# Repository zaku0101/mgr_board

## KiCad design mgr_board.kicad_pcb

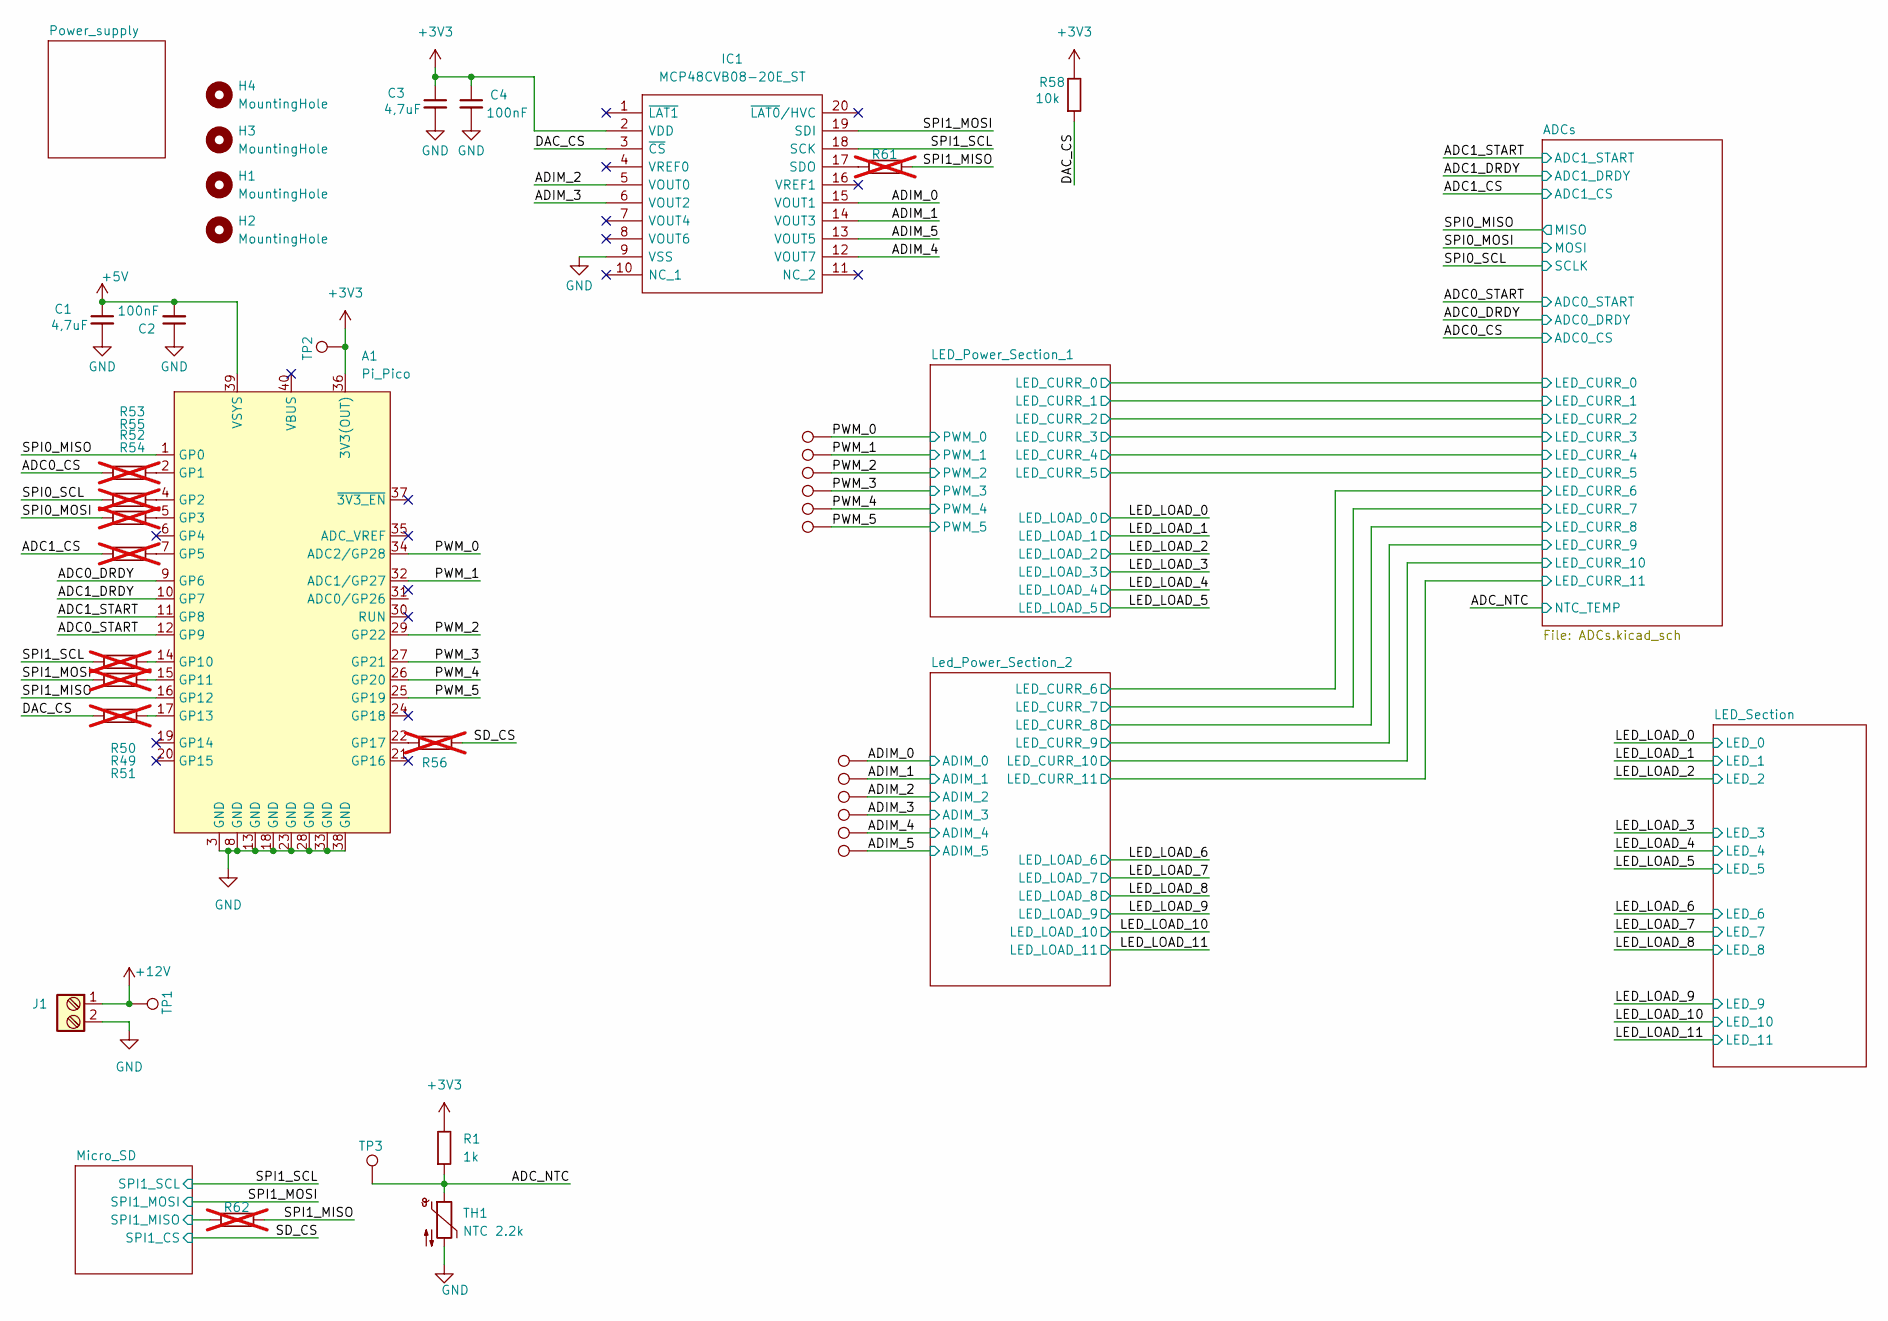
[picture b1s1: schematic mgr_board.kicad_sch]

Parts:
A1: Pi_Pico; RaspberryPi_Pico_Common_THT
C1, C3: 4,7uF; C_0603_1608Metric_Pad1.08x0.95mm_HandSolder; LCSC C19666
C2, C4: 100nF; C_0603_1608Metric_Pad1.08x0.95mm_HandSolder; LCSC C14663
H1, H2, H3, H4: MountingHole; MountingHole_3.2mm_M3
IC1: MCP48CVB08-20E_ST; TSSOP-20_4.4x6.5mm_P0.65mm; Manufacturer_Part_Number MCP48CVB08-20E/ST
J1: Screw_Terminal_2_P5.00mm; TerminalBlock_bornier-2_P5.08mm
R1: 1k; R_0603_1608Metric_Pad0.98x0.95mm_HandSolder; LCSC C21190
R49, R50, R51, R52, R53, R54, R55, R56, R61, R62: NMT; R_0402_1005Metric; not fitted
R58: 10k; R_0603_1608Metric_Pad0.98x0.95mm_HandSolder; LCSC C25804
TH1: NTC 2.2k; R_0805_2012Metric_Pad1.20x1.40mm_HandSolder
TP1, TP2, TP3, TP4, TP5, TP6, TP7, TP8, TP9, TP10, TP11, TP12, TP13, TP14, TP15: TestPoint; TestPoint_Pad_D2.0mm

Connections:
+3V3: A1.36 (3V3(OUT)), C3.1, C4.1, IC1.2 (VDD), R1.2, R58.2, TP2.1; also elsewhere on the board
+5V: A1.39 (VSYS), C1.1, C2.2; also elsewhere on the board
+12V: J1.1, TP1.1; also elsewhere on the board
/ADC0_CS: R55.2; also elsewhere on the board
/ADC0_DRDY: A1.9 (GP6); also elsewhere on the board
/ADC0_START: A1.12 (GP9); also elsewhere on the board
/ADC1_CS: R54.2; also elsewhere on the board
/ADC1_DRDY: A1.10 (GP7); also elsewhere on the board
/ADC1_START: A1.11 (GP8); also elsewhere on the board
/ADC_NTC: R1.1, TH1.1, TP3.1; also elsewhere on the board
/ADIM_0: IC1.15 (VOUT1), TP10.1; also elsewhere on the board
/ADIM_1: IC1.14 (VOUT3), TP11.1; also elsewhere on the board
/ADIM_2: IC1.5 (VOUT0), TP12.1; also elsewhere on the board
/ADIM_3: IC1.6 (VOUT2), TP13.1; also elsewhere on the board
/ADIM_4: IC1.12 (VOUT7), TP14.1; also elsewhere on the board
/ADIM_5: IC1.13 (VOUT5), TP15.1; also elsewhere on the board
/DAC_CS: IC1.3 (~CS), R51.2, R58.1
/Micro_SD/SPI1_MISO: R62.2; also elsewhere on the board
/PWM_0: A1.34 (ADC2/GP28), TP4.1; also elsewhere on the board
/PWM_1: A1.32 (ADC1/GP27), TP5.1; also elsewhere on the board
/PWM_2: A1.29 (GP22), TP6.1; also elsewhere on the board
/PWM_3: A1.27 (GP21), TP7.1; also elsewhere on the board
/PWM_4: A1.26 (GP20), TP8.1; also elsewhere on the board
/PWM_5: A1.25 (GP19), TP9.1; also elsewhere on the board
/SD_CS: R56.1; also elsewhere on the board
/SPI0_MISO: A1.1 (GP0); also elsewhere on the board
/SPI0_MOSI: R52.2; also elsewhere on the board
/SPI0_SCL: R53.2; also elsewhere on the board
/SPI1_MISO: A1.16 (GP12), R61.1, R62.1
/SPI1_MOSI: IC1.19 (SDI), R49.2; also elsewhere on the board
/SPI1_SCL: IC1.18 (SCK), R50.2; also elsewhere on the board
GND: A1.3 (GND), A1.8 (GND), A1.13 (GND), A1.18 (GND), A1.23 (GND), A1.28 (GND), A1.33 (GND), A1.38 (GND), C1.2, C2.1, C3.2, C4.2, IC1.9 (VSS), J1.2, TH1.2; also elsewhere on the board
unnamed: A1.2 (GP1), R55.1
unnamed: A1.4 (GP2), R53.1
unnamed: A1.5 (GP3), R52.1
unnamed: A1.7 (GP5), R54.1
unnamed: A1.14 (GP10), R50.1
unnamed: A1.15 (GP11), R49.1
unnamed: A1.17 (GP13), R51.1
unnamed: A1.22 (GP17), R56.2
unnamed: IC1.17 (SDO), R61.2

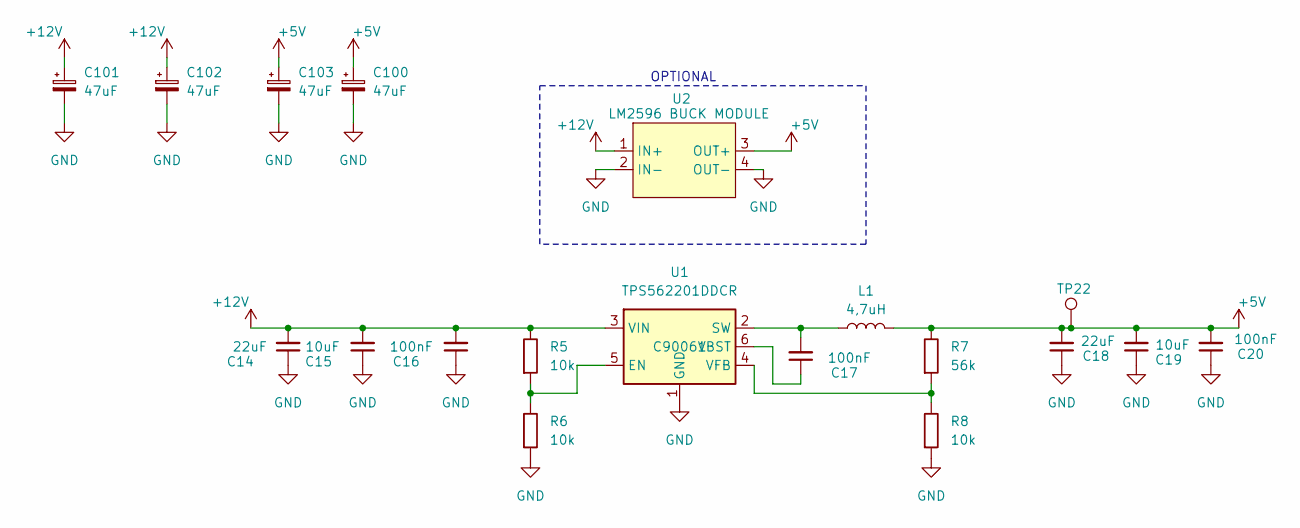
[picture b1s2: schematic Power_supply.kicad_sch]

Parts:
C14, C18: 22uF; C_0805_2012Metric_Pad1.18x1.45mm_HandSolder; LCSC C96446
C15, C19: 10uF; C_0603_1608Metric_Pad1.08x0.95mm_HandSolder; LCSC C45783
C16, C17, C20: 100nF; C_0603_1608Metric_Pad1.08x0.95mm_HandSolder; LCSC C14663
C100, C101, C102, C103: 47uF; CP_EIA-6032-15_Kemet-U_Pad2.25x2.35mm_HandSolder
L1: 4,7uH; HPIO530-4R7; LCSC C408410
R5, R6, R8: 10k; R_0603_1608Metric_Pad0.98x0.95mm_HandSolder; LCSC C25804
R7: 56k; R_0603_1608Metric_Pad0.98x0.95mm_HandSolder; LCSC C23206
TP22: TestPoint; TestPoint_Pad_D2.0mm
U1: TPS562201DDCR; SOT-23-6_Handsoldering; LCSC C90061
U2: LM2596 BUCK MODULE; LM2596 DC-DC module

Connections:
+5V: C18.2, C19.2, C20.2, C100.1, C103.1, L1.2, R7.2, TP22.1, U2.3 (OUT+); also elsewhere on the board
+12V: C14.2, C15.2, C16.2, C101.1, C102.1, R5.2, U1.3 (VIN), U2.1 (IN+); also elsewhere on the board
GND: C14.1, C15.1, C16.1, C18.1, C19.1, C20.1, C100.2, C101.2, C102.2, C103.2, R6.1, R8.1, U1.1 (GND), U2.2 (IN-), U2.4 (OUT-); also elsewhere on the board
unnamed: R5.1, R6.2, U1.5 (EN)
unnamed: C17.2, L1.1, U1.2 (SW)
unnamed: C17.1, U1.6 (VBST)
unnamed: R7.1, R8.2, U1.4 (VFB)

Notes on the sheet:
OPTIONAL

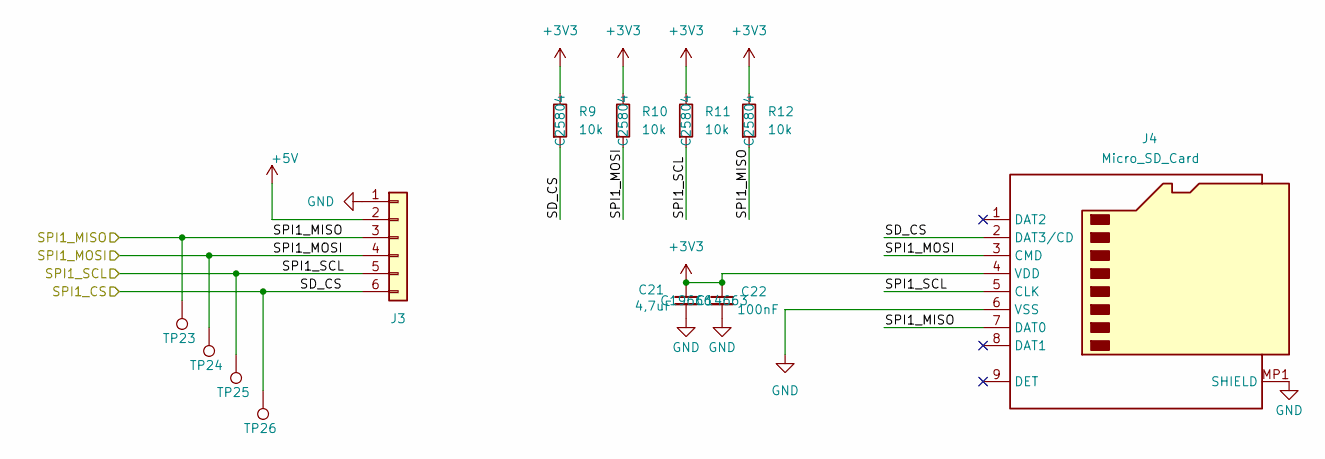
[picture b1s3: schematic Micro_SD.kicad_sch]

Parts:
C21: 4,7uF; C_0603_1608Metric_Pad1.08x0.95mm_HandSolder; LCSC C19666
C22: 100nF; C_0603_1608Metric_Pad1.08x0.95mm_HandSolder; LCSC C14663
J3: SD Card SPI Module; PinHeader_1x06_P2.54mm_Vertical; Part Number 1-0601FBV0T
J4: Micro_SD_Card; MCSPQ08ASGTR
R9, R10, R11, R12: 10k; R_0603_1608Metric_Pad0.98x0.95mm_HandSolder; LCSC C25804
TP23, TP24, TP25, TP26: TestPoint; TestPoint_Pad_D2.0mm

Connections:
+3V3: C21.1, C22.1, J4.4 (VDD), R9.2, R10.2, R11.2, R12.2; also elsewhere on the board
+5V: J3.2; also elsewhere on the board
/Micro_SD/SPI1_MISO: J3.3, J4.7 (DAT0), R12.1, TP23.1; also elsewhere on the board
/SD_CS: J3.6, J4.2 (DAT3/CD), R9.1, TP26.1; also elsewhere on the board
/SPI1_MOSI: J3.4, J4.3 (CMD), R10.1, TP24.1; also elsewhere on the board
/SPI1_SCL: J3.5, J4.5 (CLK), R11.1, TP25.1; also elsewhere on the board
GND: C21.2, C22.2, J3.1, J4.6 (VSS), J4.MP1 (SHIELD), J4.MP2 (SHIELD), J4.MP3 (SHIELD), J4.MP4 (SHIELD); also elsewhere on the board

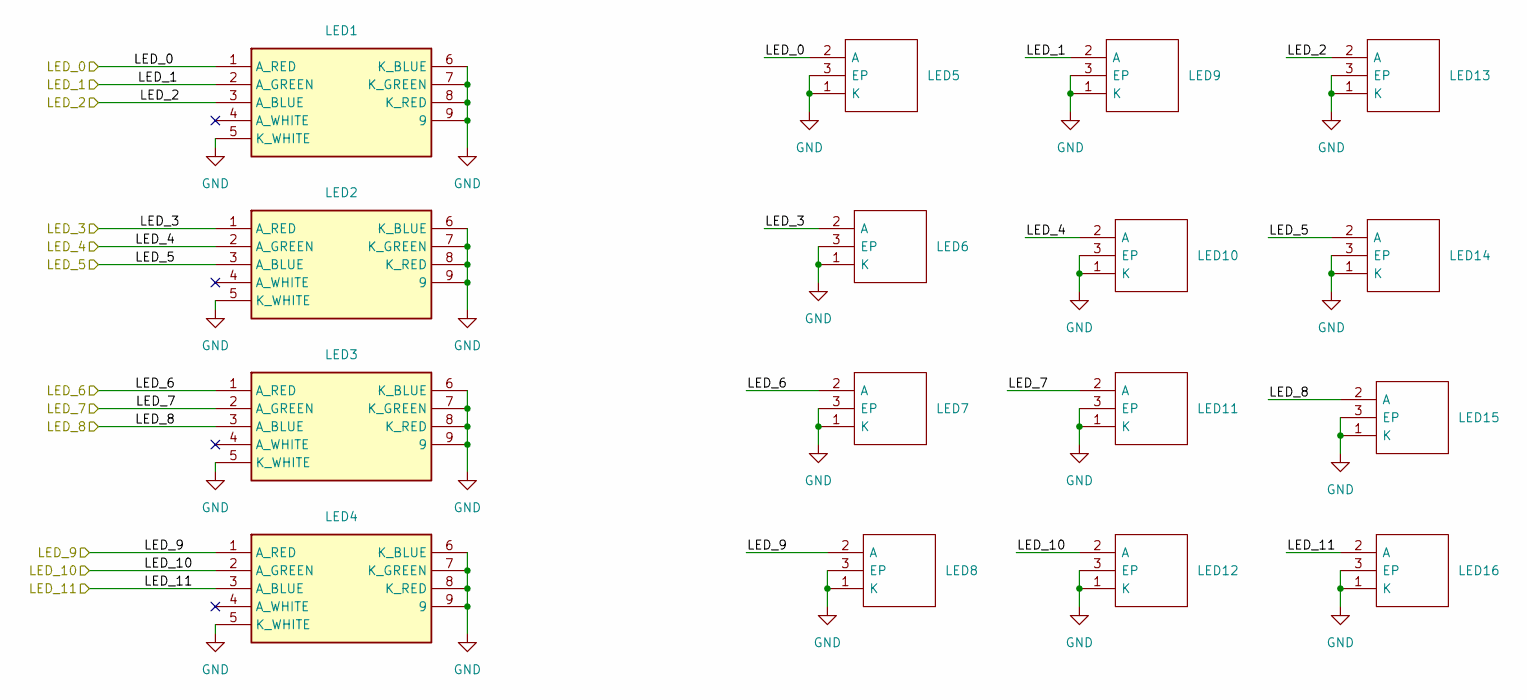
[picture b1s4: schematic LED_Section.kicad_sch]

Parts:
LED1, LED2, LED3, LED4: XPLDCL-00-0000-0000HC6AAAE7; XPLDCL; Mouser Part Number 941-XPLDCL00HC6AAAE7
LED5, LED6, LED7, LED8, LED9, LED10, LED11, LED12, LED13, LED14, LED15, LED16: JR5050CWT-E-B50EB0000-N0000001; JR5050CWT; Mouser Part Number 941-JR5050CWTEB50EBN

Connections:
/LED_LOAD_0: LED1.1 (A_RED), LED5.2 (A); also elsewhere on the board
/LED_LOAD_1: LED1.2 (A_GREEN), LED9.2 (A); also elsewhere on the board
/LED_LOAD_2: LED1.3 (A_BLUE), LED13.2 (A); also elsewhere on the board
/LED_LOAD_3: LED2.1 (A_RED), LED6.2 (A); also elsewhere on the board
/LED_LOAD_4: LED2.2 (A_GREEN), LED10.2 (A); also elsewhere on the board
/LED_LOAD_5: LED2.3 (A_BLUE), LED14.2 (A); also elsewhere on the board
/LED_LOAD_6: LED3.1 (A_RED), LED7.2 (A); also elsewhere on the board
/LED_LOAD_7: LED3.2 (A_GREEN), LED11.2 (A); also elsewhere on the board
/LED_LOAD_8: LED3.3 (A_BLUE), LED15.2 (A); also elsewhere on the board
/LED_LOAD_9: LED4.1 (A_RED), LED8.2 (A); also elsewhere on the board
/LED_LOAD_10: LED4.2 (A_GREEN), LED12.2 (A); also elsewhere on the board
/LED_LOAD_11: LED4.3 (A_BLUE), LED16.2 (A); also elsewhere on the board
GND: LED1.5 (K_WHITE), LED1.6 (K_BLUE), LED1.7 (K_GREEN), LED1.8 (K_RED), LED1.9, LED2.5 (K_WHITE), LED2.6 (K_BLUE), LED2.7 (K_GREEN), LED2.8 (K_RED), LED2.9, LED3.5 (K_WHITE), LED3.6 (K_BLUE), LED3.7 (K_GREEN), LED3.8 (K_RED), LED3.9, LED4.5 (K_WHITE), LED4.6 (K_BLUE), LED4.7 (K_GREEN), LED4.8 (K_RED), LED4.9, LED5.1 (K), LED5.3 (EP), LED6.1 (K), LED6.3 (EP), LED7.1 (K), LED7.3 (EP), LED8.1 (K), LED8.3 (EP), LED9.1 (K), LED9.3 (EP), LED10.1 (K), LED10.3 (EP), LED11.1 (K), LED11.3 (EP), LED12.1 (K), LED12.3 (EP), LED13.1 (K), LED13.3 (EP), LED14.1 (K), LED14.3 (EP), LED15.1 (K), LED15.3 (EP), LED16.1 (K), LED16.3 (EP); also elsewhere on the board

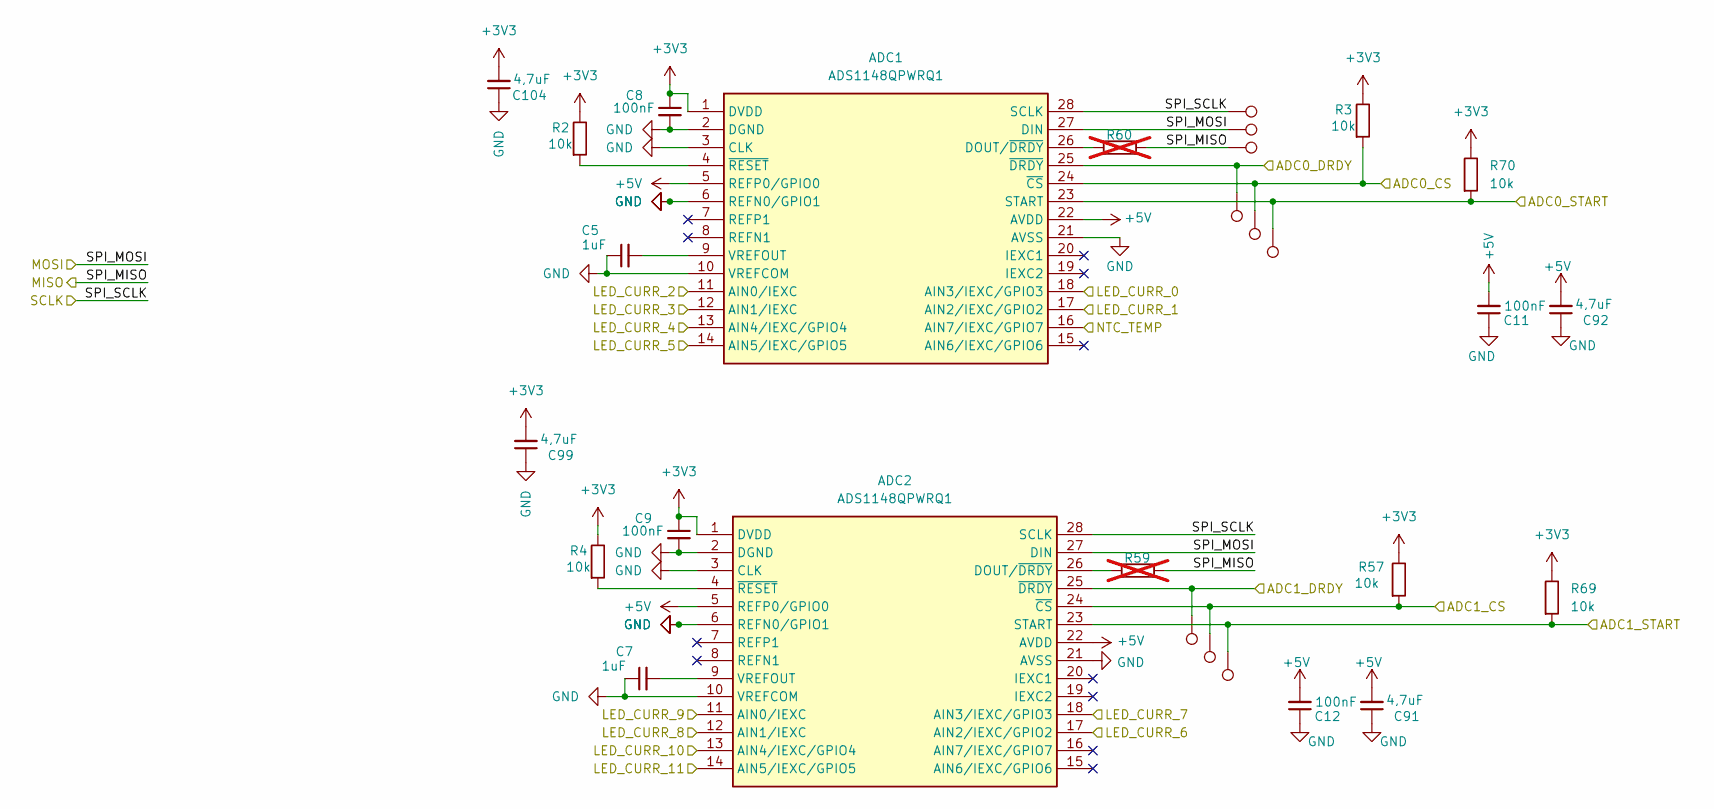
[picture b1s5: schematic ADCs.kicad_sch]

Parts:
ADC1, ADC2: ADS1148QPWRQ1; TSSOP-28_4.4x9.7mm_P0.65mm; Mouser Part Number 595-ADS1148QPWRQ1
C5, C7: 1uF; C_0603_1608Metric_Pad1.08x0.95mm_HandSolder; LCSC C15849
C8, C9, C11, C12: 100nF; C_0603_1608Metric_Pad1.08x0.95mm_HandSolder; LCSC C14663
C91, C92, C99, C104: 4,7uF; C_0603_1608Metric_Pad1.08x0.95mm_HandSolder; LCSC C19666
R2, R3, R4, R57, R69, R70: 10k; R_0603_1608Metric_Pad0.98x0.95mm_HandSolder; LCSC C25804
R59, R60: NMT; R_0402_1005Metric; not fitted
TP16, TP17, TP18, TP19, TP20, TP21, TP27, TP28, TP29: TestPoint; TestPoint_Pad_D2.0mm

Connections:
+3V3: ADC1.1 (DVDD), ADC2.1 (DVDD), C8.1, C9.1, C99.2, C104.2, R2.2, R3.2, R4.2, R57.2, R69.2, R70.2; also elsewhere on the board
+5V: ADC1.5 (REFP0/GPIO0), ADC1.22 (AVDD), ADC2.5 (REFP0/GPIO0), ADC2.22 (AVDD), C11.2, C12.2, C91.2, C92.2; also elsewhere on the board
/ADC0_CS: ADC1.24 (~CS), R3.1, TP20.1; also elsewhere on the board
/ADC0_DRDY: ADC1.25 (~DRDY), TP19.1; also elsewhere on the board
/ADC0_START: ADC1.23 (START), R70.1, TP29.1; also elsewhere on the board
/ADC1_CS: ADC2.24 (~CS), R57.1, TP27.1; also elsewhere on the board
/ADC1_DRDY: ADC2.25 (~DRDY), TP28.1; also elsewhere on the board
/ADC1_START: ADC2.23 (START), R69.1, TP21.1; also elsewhere on the board
/ADC_NTC: ADC1.16 (AIN7/IEXC/GPIO7); also elsewhere on the board
/ADCs/LED_CURR_0: ADC1.18 (AIN3/IEXC/GPIO3); also elsewhere on the board
/ADCs/LED_CURR_1: ADC1.17 (AIN2/IEXC/GPIO2); also elsewhere on the board
/ADCs/LED_CURR_2: ADC1.11 (AIN0/IEXC); also elsewhere on the board
/ADCs/LED_CURR_3: ADC1.12 (AIN1/IEXC); also elsewhere on the board
/ADCs/LED_CURR_4: ADC1.13 (AIN4/IEXC/GPIO4); also elsewhere on the board
/ADCs/LED_CURR_5: ADC1.14 (AIN5/IEXC/GPIO5); also elsewhere on the board
/ADCs/LED_CURR_6: ADC2.17 (AIN2/IEXC/GPIO2); also elsewhere on the board
/ADCs/LED_CURR_7: ADC2.18 (AIN3/IEXC/GPIO3); also elsewhere on the board
/ADCs/LED_CURR_8: ADC2.12 (AIN1/IEXC); also elsewhere on the board
/ADCs/LED_CURR_9: ADC2.11 (AIN0/IEXC); also elsewhere on the board
/ADCs/LED_CURR_10: ADC2.13 (AIN4/IEXC/GPIO4); also elsewhere on the board
/ADCs/LED_CURR_11: ADC2.14 (AIN5/IEXC/GPIO5); also elsewhere on the board
/SPI0_MISO: R59.1, R60.1, TP18.1; also elsewhere on the board
/SPI0_MOSI: ADC1.27 (DIN), ADC2.27 (DIN), TP17.1; also elsewhere on the board
/SPI0_SCL: ADC1.28 (SCLK), ADC2.28 (SCLK), TP16.1; also elsewhere on the board
GND: ADC1.2 (DGND), ADC1.3 (CLK), ADC1.6 (REFN0/GPIO1), ADC1.10 (VREFCOM), ADC1.21 (AVSS), ADC2.2 (DGND), ADC2.3 (CLK), ADC2.6 (REFN0/GPIO1), ADC2.10 (VREFCOM), ADC2.21 (AVSS), C5.1, C7.1, C8.2, C9.2, C11.1, C12.1, C91.1, C92.1, C99.1, C104.1; also elsewhere on the board
unnamed: ADC1.26 (DOUT/~DRDY), R60.2
unnamed: ADC1.9 (VREFOUT), C5.2
unnamed: ADC1.4 (~RESET), R2.1
unnamed: ADC2.26 (DOUT/~DRDY), R59.2
unnamed: ADC2.9 (VREFOUT), C7.2
unnamed: ADC2.4 (~RESET), R4.1

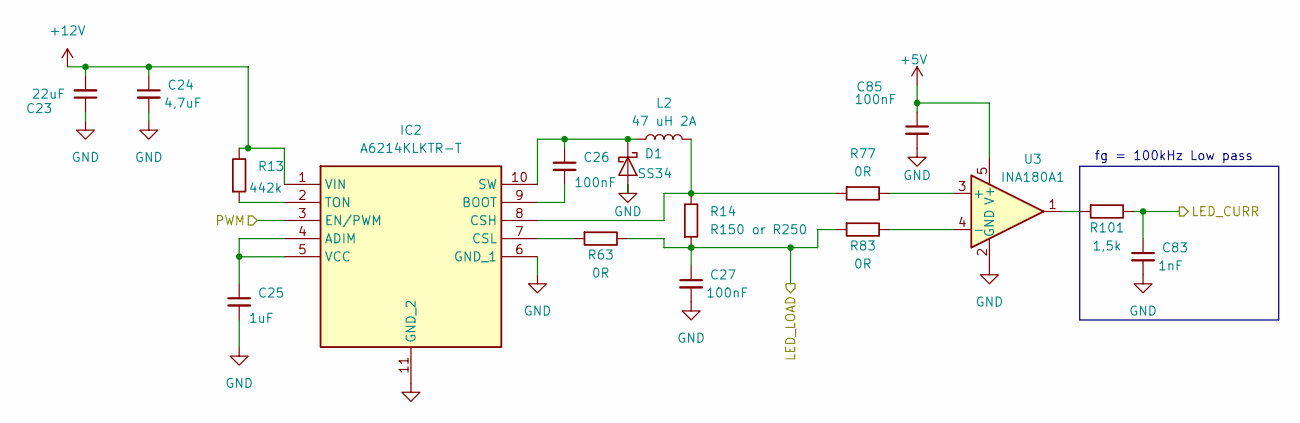
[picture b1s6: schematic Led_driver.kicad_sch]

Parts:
C23: 22uF; C_0805_2012Metric_Pad1.18x1.45mm_HandSolder; LCSC C96446
C24: 4,7uF; C_0603_1608Metric_Pad1.08x0.95mm_HandSolder; LCSC C19666
C25: 1uF; C_0603_1608Metric_Pad1.08x0.95mm_HandSolder; LCSC C15849
C26, C27, C85: 100nF; C_0603_1608Metric_Pad1.08x0.95mm_HandSolder; LCSC C14663
C83: 1nF; C_0402_1005Metric_Pad0.74x0.62mm_HandSolder; LCSC C1523
D1: SS34; D_SMA; Part Number B140-E3/5AT; JLCPCB ID C15759
IC2: A6214KLKTR-T; SOP100P600X165-11N; Manufacturer_Part_Number A6214KLKTR-T; LCSC C146400
L2: 47 uH 2A; DR125-470-R; LCSC C5127262
R13: 442k; R_0603_1608Metric_Pad0.98x0.95mm_HandSolder; LCSC C23175
R14: R150 or R250; R_2512_6332Metric_Pad1.40x3.35mm_HandSolder
R63, R77, R83: 0R; R_0402_1005Metric_Pad0.72x0.64mm_HandSolder; LCSC C17168
R101: 1,5k; R_0402_1005Metric_Pad0.72x0.64mm_HandSolder; LCSC C25867
U3: INA180A1; SOT-23-5; LCSC C122228

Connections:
+5V: C85.1, U3.5 (V+); also elsewhere on the board
+12V: C23.2, C24.1, IC2.1 (VIN), R13.2; also elsewhere on the board
/ADCs/LED_CURR_0: C83.1, R101.2; also elsewhere on the board
/LED_LOAD_0: C27.1, R14.1, R63.2, R83.1; also elsewhere on the board
/PWM_0: IC2.3 (EN/PWM); also elsewhere on the board
GND: C23.1, C24.2, C25.2, C27.2, C83.2, C85.2, D1.2 (A), IC2.6 (GND_1), IC2.11 (GND_2), U3.2 (GND); also elsewhere on the board
unnamed: C26.1, D1.1 (K), IC2.10 (SW), L2.1
unnamed: C25.1, IC2.4 (ADIM), IC2.5 (VCC)
unnamed: C26.2, IC2.9 (BOOT)
unnamed: IC2.8 (CSH), L2.2, R14.2, R77.1
unnamed: IC2.7 (CSL), R63.1
unnamed: IC2.2 (TON), R13.1
unnamed: R101.1, U3.1
unnamed: R77.2, U3.3 (+)
unnamed: R83.2, U3.4 (-)

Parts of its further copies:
C28, C33, C38, C43, C48: 22uF; C_0805_2012Metric_Pad1.18x1.45mm_HandSolder; LCSC C96446
C29, C34, C39, C44, C49: 4,7uF; C_0603_1608Metric_Pad1.08x0.95mm_HandSolder; LCSC C19666
C30, C35, C40, C45, C50: 1uF; C_0603_1608Metric_Pad1.08x0.95mm_HandSolder; LCSC C15849
C31, C32, C36, C37, C41, C42, C46, C47, C51, C52, C86, C87, C88, C89, C90: 100nF; C_0603_1608Metric_Pad1.08x0.95mm_HandSolder; LCSC C14663
C84, C105, C106, C107, C108: 1nF; C_0402_1005Metric_Pad0.74x0.62mm_HandSolder; LCSC C1523
D2, D3, D4, D5, D6: SS34; D_SMA; Part Number B140-E3/5AT; JLCPCB ID C15759
IC3, IC4, IC5, IC6, IC7: A6214KLKTR-T; SOP100P600X165-11N; Manufacturer_Part_Number A6214KLKTR-T; LCSC C146400
L3, L4, L5, L6, L7: 47 uH 2A; DR125-470-R; LCSC C5127262
R15, R17, R19, R21, R23: 442k; R_0603_1608Metric_Pad0.98x0.95mm_HandSolder; LCSC C23175
R16, R18, R20, R22, R24: R150 or R250; R_2512_6332Metric_Pad1.40x3.35mm_HandSolder
R64, R65, R66, R67, R68, R78, R79, R80, R81, R82, R84, R85, R86, R87, R88: 0R; R_0402_1005Metric_Pad0.72x0.64mm_HandSolder; LCSC C17168
R102, R103, R104, R105, R106: 1,5k; R_0402_1005Metric_Pad0.72x0.64mm_HandSolder; LCSC C25867
U4, U5, U6, U7, U8: INA180A1; SOT-23-5; LCSC C122228

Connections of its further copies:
+5V: C86.1, C87.1, C88.1, C89.1, C90.1, U4.5 (V+), U5.5 (V+), U6.5 (V+), U7.5 (V+), U8.5 (V+); also elsewhere on the board
+12V: C28.2, C29.1, C33.2, C34.1, C38.2, C39.1, C43.2, C44.1, C48.2, C49.1, IC3.1 (VIN), IC4.1 (VIN), IC5.1 (VIN), IC6.1 (VIN), IC7.1 (VIN), R15.2, R17.2, R19.2, R21.2, R23.2; also elsewhere on the board
/ADCs/LED_CURR_1: C106.1, R104.2; also elsewhere on the board
/ADCs/LED_CURR_2: C84.1, R102.2; also elsewhere on the board
/ADCs/LED_CURR_3: C107.1, R105.2; also elsewhere on the board
/ADCs/LED_CURR_4: C105.1, R103.2; also elsewhere on the board
/ADCs/LED_CURR_5: C108.1, R106.2; also elsewhere on the board
/LED_LOAD_1: C42.1, R20.1, R66.2, R86.1; also elsewhere on the board
/LED_LOAD_2: C32.1, R16.1, R64.2, R84.1; also elsewhere on the board
/LED_LOAD_3: C47.1, R22.1, R67.2, R87.1; also elsewhere on the board
/LED_LOAD_4: C37.1, R18.1, R65.2, R85.1; also elsewhere on the board
/LED_LOAD_5: C52.1, R24.1, R68.2, R88.1; also elsewhere on the board
/PWM_1: IC5.3 (EN/PWM); also elsewhere on the board
/PWM_2: IC3.3 (EN/PWM); also elsewhere on the board
/PWM_3: IC6.3 (EN/PWM); also elsewhere on the board
/PWM_4: IC4.3 (EN/PWM); also elsewhere on the board
/PWM_5: IC7.3 (EN/PWM); also elsewhere on the board
GND: C28.1, C29.2, C30.2, C32.2, C33.1, C34.2, C35.2, C37.2, C38.1, C39.2, C40.2, C42.2, C43.1, C44.2, C45.2, C47.2, C48.1, C49.2, C50.2, C52.2, C84.2, C86.2, C87.2, C88.2, C89.2, C90.2, C105.2, C106.2, C107.2, C108.2, D2.2 (A), D3.2 (A), D4.2 (A), D5.2 (A), D6.2 (A), IC3.6 (GND_1), IC3.11 (GND_2), IC4.6 (GND_1), IC4.11 (GND_2), IC5.6 (GND_1), IC5.11 (GND_2), IC6.6 (GND_1), IC6.11 (GND_2), IC7.6 (GND_1), IC7.11 (GND_2), U4.2 (GND), U5.2 (GND), U6.2 (GND), U7.2 (GND), U8.2 (GND); also elsewhere on the board
unnamed: C31.1, D2.1 (K), IC3.10 (SW), L3.1
unnamed: C36.1, D3.1 (K), IC4.10 (SW), L4.1
unnamed: C41.1, D4.1 (K), IC5.10 (SW), L5.1
unnamed: C46.1, D5.1 (K), IC6.10 (SW), L6.1
unnamed: C51.1, D6.1 (K), IC7.10 (SW), L7.1
unnamed: C30.1, IC3.4 (ADIM), IC3.5 (VCC)
unnamed: C31.2, IC3.9 (BOOT)
unnamed: IC3.8 (CSH), L3.2, R16.2, R78.1
unnamed: IC3.7 (CSL), R64.1
unnamed: IC3.2 (TON), R15.1
unnamed: C35.1, IC4.4 (ADIM), IC4.5 (VCC)
unnamed: C36.2, IC4.9 (BOOT)
unnamed: IC4.8 (CSH), L4.2, R18.2, R79.1
unnamed: IC4.7 (CSL), R65.1
unnamed: IC4.2 (TON), R17.1
unnamed: C40.1, IC5.4 (ADIM), IC5.5 (VCC)
unnamed: C41.2, IC5.9 (BOOT)
unnamed: IC5.8 (CSH), L5.2, R20.2, R80.1
unnamed: IC5.7 (CSL), R66.1
unnamed: IC5.2 (TON), R19.1
unnamed: C45.1, IC6.4 (ADIM), IC6.5 (VCC)
unnamed: C46.2, IC6.9 (BOOT)
unnamed: IC6.8 (CSH), L6.2, R22.2, R81.1
unnamed: IC6.7 (CSL), R67.1
unnamed: IC6.2 (TON), R21.1
unnamed: C50.1, IC7.4 (ADIM), IC7.5 (VCC)
unnamed: C51.2, IC7.9 (BOOT)
unnamed: IC7.8 (CSH), L7.2, R24.2, R82.1
unnamed: IC7.7 (CSL), R68.1
unnamed: IC7.2 (TON), R23.1
unnamed: R102.1, U4.1
unnamed: R103.1, U5.1
unnamed: R104.1, U6.1
unnamed: R105.1, U7.1
unnamed: R106.1, U8.1
unnamed: R78.2, U4.3 (+)
unnamed: R84.2, U4.4 (-)
unnamed: R79.2, U5.3 (+)
unnamed: R85.2, U5.4 (-)
unnamed: R80.2, U6.3 (+)
unnamed: R86.2, U6.4 (-)
unnamed: R81.2, U7.3 (+)
unnamed: R87.2, U7.4 (-)
unnamed: R82.2, U8.3 (+)
unnamed: R88.2, U8.4 (-)

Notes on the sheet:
fg = 100kHz Low pass

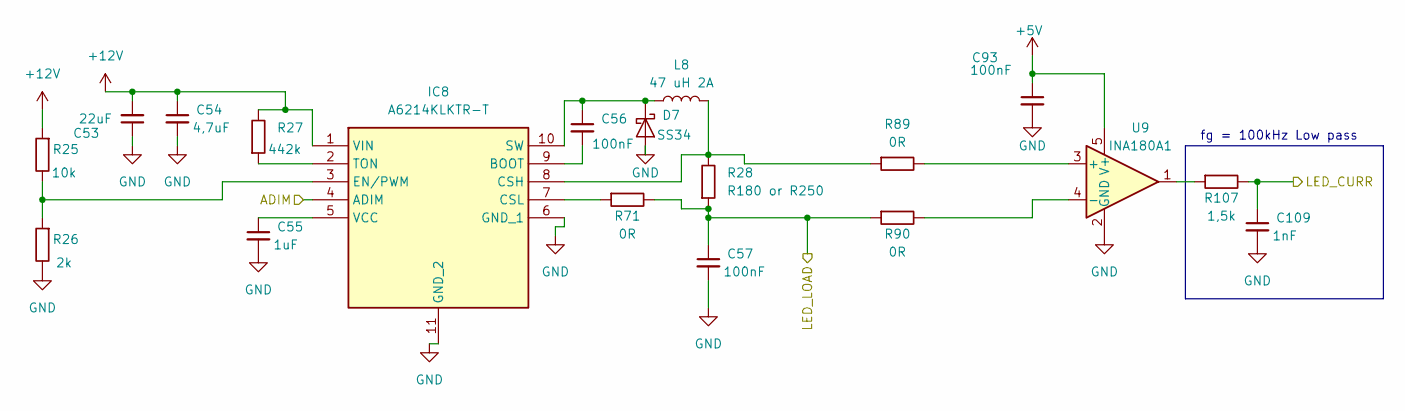
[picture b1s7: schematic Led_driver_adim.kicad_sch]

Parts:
C53: 22uF; C_0805_2012Metric_Pad1.18x1.45mm_HandSolder; LCSC C96446
C54: 4,7uF; C_0603_1608Metric_Pad1.08x0.95mm_HandSolder; LCSC C19666
C55: 1uF; C_0603_1608Metric_Pad1.08x0.95mm_HandSolder; LCSC C15849
C56, C57, C93: 100nF; C_0603_1608Metric_Pad1.08x0.95mm_HandSolder; LCSC C14663
C109: 1nF; C_0402_1005Metric_Pad0.74x0.62mm_HandSolder; LCSC C1523
D7: SS34; D_SMA; Part Number B140-E3/5AT; JLCPCB ID C15759
IC8: A6214KLKTR-T; SOP100P600X165-11N; Manufacturer_Part_Number A6214KLKTR-T; LCSC C146400
L8: 47 uH 2A; DR125-470-R; LCSC C5127262
R25: 10k; R_0603_1608Metric_Pad0.98x0.95mm_HandSolder; LCSC C25804
R26: 2k; R_0603_1608Metric_Pad0.98x0.95mm_HandSolder; LCSC C22975
R27: 442k; R_0603_1608Metric_Pad0.98x0.95mm_HandSolder; LCSC C23175
R28: R180 or R250; R_2512_6332Metric_Pad1.40x3.35mm_HandSolder
R71, R89, R90: 0R; R_0402_1005Metric_Pad0.72x0.64mm_HandSolder; LCSC C17168
R107: 1,5k; R_0402_1005Metric_Pad0.72x0.64mm_HandSolder; LCSC C25867
U9: INA180A1; SOT-23-5

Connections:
+5V: C93.1, U9.5 (V+); also elsewhere on the board
+12V: C53.2, C54.1, IC8.1 (VIN), R25.1, R27.2; also elsewhere on the board
/ADCs/LED_CURR_6: C109.1, R107.2; also elsewhere on the board
/ADIM_0: IC8.4 (ADIM); also elsewhere on the board
/LED_LOAD_6: C57.1, R28.1, R71.2, R90.1; also elsewhere on the board
GND: C53.1, C54.2, C55.2, C57.2, C93.2, C109.2, D7.2 (A), IC8.6 (GND_1), IC8.11 (GND_2), R26.2, U9.2 (GND); also elsewhere on the board
unnamed: C56.1, D7.1 (K), IC8.10 (SW), L8.1
unnamed: C56.2, IC8.9 (BOOT)
unnamed: IC8.8 (CSH), L8.2, R28.2, R89.1
unnamed: IC8.7 (CSL), R71.1
unnamed: IC8.3 (EN/PWM), R25.2, R26.1
unnamed: IC8.2 (TON), R27.1
unnamed: C55.1, IC8.5 (VCC)
unnamed: R107.1, U9.1
unnamed: R89.2, U9.3 (+)
unnamed: R90.2, U9.4 (-)

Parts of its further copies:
C58, C63, C68, C73, C78: 22uF; C_0805_2012Metric_Pad1.18x1.45mm_HandSolder; LCSC C96446
C59, C64, C69, C74, C79: 4,7uF; C_0603_1608Metric_Pad1.08x0.95mm_HandSolder; LCSC C19666
C60, C65, C70, C75, C80: 1uF; C_0603_1608Metric_Pad1.08x0.95mm_HandSolder; LCSC C15849
C61, C62, C66, C67, C71, C72, C76, C77, C81, C82, C94, C95, C96, C97, C98: 100nF; C_0603_1608Metric_Pad1.08x0.95mm_HandSolder; LCSC C14663
C110, C111, C112, C113, C114: 1nF; C_0402_1005Metric_Pad0.74x0.62mm_HandSolder; LCSC C1523
D8, D9, D10, D11, D12: SS34; D_SMA; Part Number B140-E3/5AT; JLCPCB ID C15759
IC9, IC10, IC11, IC12, IC13: A6214KLKTR-T; SOP100P600X165-11N; Manufacturer_Part_Number A6214KLKTR-T; LCSC C146400
L9, L10, L11, L12, L13: 47 uH 2A; DR125-470-R; LCSC C5127262
R29, R33, R37, R41, R45: 10k; R_0603_1608Metric_Pad0.98x0.95mm_HandSolder; LCSC C25804
R30, R34, R38, R42, R46: 2k; R_0603_1608Metric_Pad0.98x0.95mm_HandSolder; LCSC C22975
R31, R35, R39, R43, R47: 442k; R_0603_1608Metric_Pad0.98x0.95mm_HandSolder; LCSC C23175
R32, R36, R40, R44, R48: R180 or R250; R_2512_6332Metric_Pad1.40x3.35mm_HandSolder
R72, R73, R74, R75, R76, R91, R92, R93, R94, R95, R96, R97, R98, R99, R100: 0R; R_0402_1005Metric_Pad0.72x0.64mm_HandSolder; LCSC C17168
R108, R109, R110, R111, R112: 1,5k; R_0402_1005Metric_Pad0.72x0.64mm_HandSolder; LCSC C25867
U10, U11, U12, U13, U14: INA180A1; SOT-23-5

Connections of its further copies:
+5V: C94.1, C95.1, C96.1, C97.1, C98.1, U10.5 (V+), U11.5 (V+), U12.5 (V+), U13.5 (V+), U14.5 (V+); also elsewhere on the board
+12V: C58.2, C59.1, C63.2, C64.1, C68.2, C69.1, C73.2, C74.1, C78.2, C79.1, IC9.1 (VIN), IC10.1 (VIN), IC11.1 (VIN), IC12.1 (VIN), IC13.1 (VIN), R29.1, R31.2, R33.1, R35.2, R37.1, R39.2, R41.1, R43.2, R45.1, R47.2; also elsewhere on the board
/ADCs/LED_CURR_7: C110.1, R108.2; also elsewhere on the board
/ADCs/LED_CURR_8: C111.1, R109.2; also elsewhere on the board
/ADCs/LED_CURR_9: C112.1, R110.2; also elsewhere on the board
/ADCs/LED_CURR_10: C113.1, R111.2; also elsewhere on the board
/ADCs/LED_CURR_11: C114.1, R112.2; also elsewhere on the board
/ADIM_1: IC9.4 (ADIM); also elsewhere on the board
/ADIM_2: IC10.4 (ADIM); also elsewhere on the board
/ADIM_3: IC11.4 (ADIM); also elsewhere on the board
/ADIM_4: IC12.4 (ADIM); also elsewhere on the board
/ADIM_5: IC13.4 (ADIM); also elsewhere on the board
/LED_LOAD_7: C62.1, R32.1, R72.2, R92.1; also elsewhere on the board
/LED_LOAD_8: C67.1, R36.1, R73.2, R94.1; also elsewhere on the board
/LED_LOAD_9: C72.1, R40.1, R74.2, R96.1; also elsewhere on the board
/LED_LOAD_10: C77.1, R44.1, R75.2, R98.1; also elsewhere on the board
/LED_LOAD_11: C82.1, R48.1, R76.2, R100.1; also elsewhere on the board
GND: C58.1, C59.2, C60.2, C62.2, C63.1, C64.2, C65.2, C67.2, C68.1, C69.2, C70.2, C72.2, C73.1, C74.2, C75.2, C77.2, C78.1, C79.2, C80.2, C82.2, C94.2, C95.2, C96.2, C97.2, C98.2, C110.2, C111.2, C112.2, C113.2, C114.2, D8.2 (A), D9.2 (A), D10.2 (A), D11.2 (A), D12.2 (A), IC9.6 (GND_1), IC9.11 (GND_2), IC10.6 (GND_1), IC10.11 (GND_2), IC11.6 (GND_1), IC11.11 (GND_2), IC12.6 (GND_1), IC12.11 (GND_2), IC13.6 (GND_1), IC13.11 (GND_2), R30.2, R34.2, R38.2, R42.2, R46.2, U10.2 (GND), U11.2 (GND), U12.2 (GND), U13.2 (GND), U14.2 (GND); also elsewhere on the board
unnamed: C61.1, D8.1 (K), IC9.10 (SW), L9.1
unnamed: C66.1, D9.1 (K), IC10.10 (SW), L10.1
unnamed: C71.1, D10.1 (K), IC11.10 (SW), L11.1
unnamed: C76.1, D11.1 (K), IC12.10 (SW), L12.1
unnamed: C81.1, D12.1 (K), IC13.10 (SW), L13.1
unnamed: C61.2, IC9.9 (BOOT)
unnamed: IC9.8 (CSH), L9.2, R32.2, R91.1
unnamed: IC9.7 (CSL), R72.1
unnamed: IC9.3 (EN/PWM), R29.2, R30.1
unnamed: IC9.2 (TON), R31.1
unnamed: C60.1, IC9.5 (VCC)
unnamed: C66.2, IC10.9 (BOOT)
unnamed: IC10.8 (CSH), L10.2, R36.2, R93.1
unnamed: IC10.7 (CSL), R73.1
unnamed: IC10.3 (EN/PWM), R33.2, R34.1
unnamed: IC10.2 (TON), R35.1
unnamed: C65.1, IC10.5 (VCC)
unnamed: C71.2, IC11.9 (BOOT)
unnamed: IC11.8 (CSH), L11.2, R40.2, R95.1
unnamed: IC11.7 (CSL), R74.1
unnamed: IC11.3 (EN/PWM), R37.2, R38.1
unnamed: IC11.2 (TON), R39.1
unnamed: C70.1, IC11.5 (VCC)
unnamed: C76.2, IC12.9 (BOOT)
unnamed: IC12.8 (CSH), L12.2, R44.2, R97.1
unnamed: IC12.7 (CSL), R75.1
unnamed: IC12.3 (EN/PWM), R41.2, R42.1
unnamed: IC12.2 (TON), R43.1
unnamed: C75.1, IC12.5 (VCC)
unnamed: C81.2, IC13.9 (BOOT)
unnamed: IC13.8 (CSH), L13.2, R48.2, R99.1
unnamed: IC13.7 (CSL), R76.1
unnamed: IC13.3 (EN/PWM), R45.2, R46.1
unnamed: IC13.2 (TON), R47.1
unnamed: C80.1, IC13.5 (VCC)
unnamed: R108.1, U10.1
unnamed: R109.1, U11.1
unnamed: R110.1, U12.1
unnamed: R111.1, U13.1
unnamed: R112.1, U14.1
unnamed: R91.2, U10.3 (+)
unnamed: R92.2, U10.4 (-)
unnamed: R93.2, U11.3 (+)
unnamed: R94.2, U11.4 (-)
unnamed: R95.2, U12.3 (+)
unnamed: R96.2, U12.4 (-)
unnamed: R97.2, U13.3 (+)
unnamed: R98.2, U13.4 (-)
unnamed: R99.2, U14.3 (+)
unnamed: R100.2, U14.4 (-)

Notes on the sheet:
fg = 100kHz Low pass
